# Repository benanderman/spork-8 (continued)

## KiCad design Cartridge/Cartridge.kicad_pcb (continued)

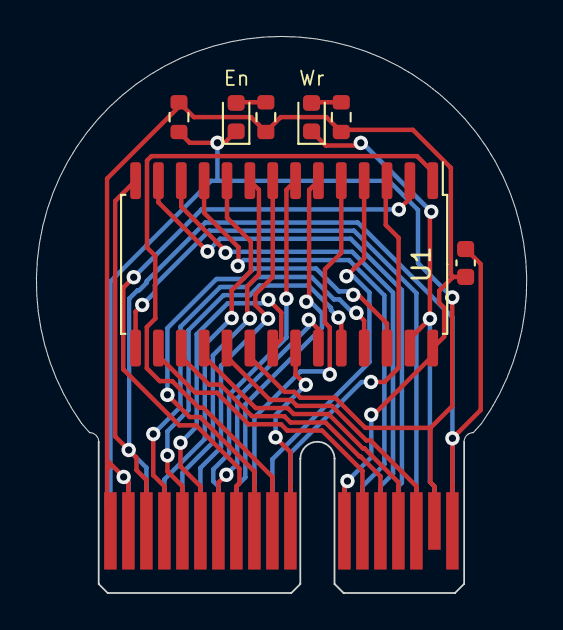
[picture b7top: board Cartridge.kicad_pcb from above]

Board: 2 copper layers, 27.2 x 30.9 mm, 8 parts (0 on the bottom side), 30 nets.

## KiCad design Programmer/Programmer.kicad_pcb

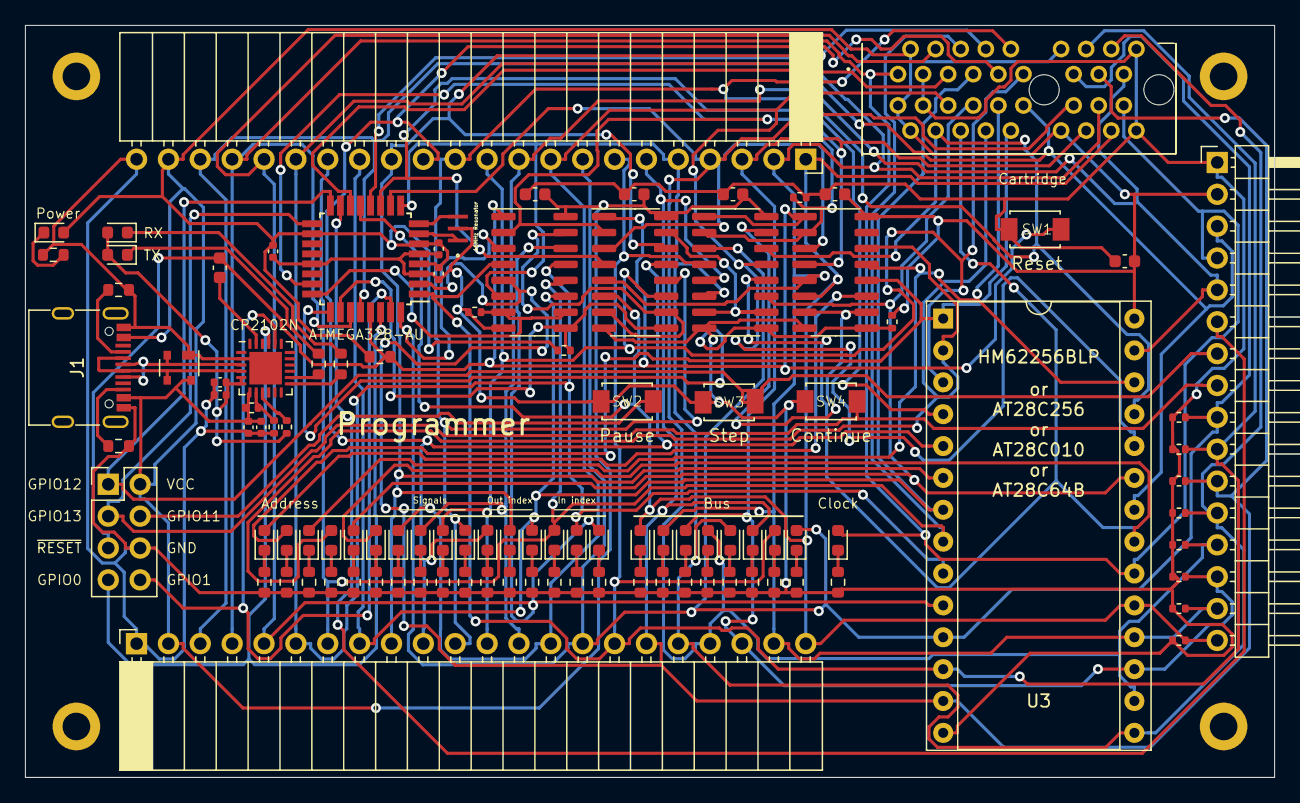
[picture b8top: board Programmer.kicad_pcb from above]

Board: 2 copper layers, 99.6 x 59.9 mm, 110 parts (0 on the bottom side), 82 nets.

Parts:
16MHz1: Resonator; OSC_CSTCE16M0V53-R0
C1, C2, C3, C4, C6: 4.7uF; C_0402_1005Metric
C5, C7: 0.1uF; C_0402_1005Metric
C8, C9, C10, C11, C12, C13: 0.1uF; C_0603_1608Metric
D1, D4: GREEN; LED_0603_1608Metric
D2: SP0503BAHT; SOT-143
D3: RED; LED_0603_1608Metric
D5, D6, D7, D8, D9, D10, D11, D12, D13, D14, D15, D16, D17, D18, D19, D20, D21, D22, D23, D24, D25, D26, D27, D28, D29: LED; LED_0603_1608Metric
HOLE1, HOLE2, HOLE3, HOLE4: MountingHole_2.2mm_M2_DIN965_Pad
J1: USB_C_Receptacle_USB2.0; USB_C_Receptacle_G-Switch_GT-USB-7010ASV
J2, J3: Conn_01x22; PinSocket_1x22_P2.54mm_Horizontal
J4: Conn_01x16; PinHeader_1x16_P2.54mm_Horizontal
J5: 3183-10200P1T; 318310200P1T
J6: Conn_02x04_Odd_Even; PinHeader_2x04_P2.54mm_Vertical
R1, R9: 47k; R_0603_1608Metric
R2, R8, R10, R11, R12, R13, R14, R15, R16, R17, R18, R19, R20, R21, R22, R23, R24, R25, R26, R27, R28, R29, R30, R31, R32, R33, R34: 10k; R_0603_1608Metric
R3, R4: 5.1k; R_0603_1608Metric
R5: 22.1k; R_0402_1005Metric
R6: 47.5k; R_0402_1005Metric
R7: 1k; R_0402_1005Metric
R35, R36, R37, R38, R39, R40, R41, R42, R43, R44, R45, R46: 10k; R_0402_1005Metric
SW1: RESET; SW_TS-1088-AR02016
SW2: PAUSE; SW_TS-1088-AR02016
SW3: STEP; SW_TS-1088-AR02016
SW4: CONTINUE; SW_TS-1088-AR02016
U1: ATMEGA328-AU; TQFP-32_7x7mm_P0.8mm
U2: CP2102N-Axx-xQFN24; QFN-24-1EP_4x4mm_P0.5mm_EP2.6x2.6mm
U3: HM62256BLP; DIP-28_W15.24mm_Socket
U4, U5, U6, U7: 74HC161; SOIC-16_3.9x9.9mm_P1.27mm

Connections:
A0: D5.2 (A), J2.5, J3.18, J5.A4, U3.10 (A0), U4.14 (Q0)
A1: D6.2 (A), J2.6, J3.17, J5.A5, U3.9 (A1), U4.13 (Q1)
A2: D7.2 (A), J2.7, J3.16, J5.A6, U3.8 (A2), U4.12 (Q2)
A3: D8.2 (A), J2.8, J3.15, J5.A7, U3.7 (A3), U4.11 (Q3)
A4: D9.2 (A), J2.9, J3.14, J5.A8, U3.6 (A4), U5.14 (Q0)
A5: D10.2 (A), J2.10, J3.13, J5.A9, U3.5 (A5), U5.13 (Q1)
A6: D11.2 (A), J2.11, J3.12, J5.A10, U3.4 (A6), U5.12 (Q2)
A7: D12.2 (A), J2.12, J3.11, J5.A11, U3.3 (A7), U5.11 (Q3)
A8: D13.2 (A), J2.13, J3.10, J5.B4, U3.25 (A8), U6.14 (Q0)
A9: D14.2 (A), J2.14, J3.9, J5.B5, U3.24 (A9), U6.13 (Q1)
A10: D15.2 (A), J5.B6, U3.21 (A10), U6.12 (Q2)
A11: D16.2 (A), J5.B7, U3.23 (A11), U6.11 (Q3)
A12: D17.2 (A), J5.B8, U3.2 (A12), U7.14 (Q0)
A13: D18.2 (A), J5.B9, U3.26 (A13), U7.13 (Q1)
A14: D19.2 (A), J5.B10, U3.1 (A14), U7.12 (Q2)
A15: D20.2 (A), U7.11 (Q3)
ADDR_CLOCK: R45.2, U1.23 (PC0), U4.2 (CP), U5.2 (CP), U6.2 (CP), U7.2 (CP)
ADDR_COUNT: R46.2, U1.24 (PC1), U4.7 (CEP), U4.10 (CET)
BUS0: D21.2 (A), J2.15, J3.8, J4.9, J5.A13, R35.2, U1.32 (PD2), U3.11 (Q0), U4.3 (D0), U6.3 (D0)
BUS1: D22.2 (A), J2.16, J3.7, J4.10, J5.A14, R36.2, U1.1 (PD3), U3.12 (Q1), U4.4 (D1), U6.4 (D1)
BUS2: D23.2 (A), J2.17, J3.6, J4.11, J5.A15, R37.2, U1.2 (PD4), U3.13 (Q2), U4.5 (D2), U6.5 (D2)
BUS3: D24.2 (A), J2.18, J3.5, J4.12, J5.A16, R38.2, U1.9 (PD5), U3.15 (Q3), U4.6 (D3), U6.6 (D3)
BUS4: D25.2 (A), J2.19, J3.4, J4.13, J5.B13, R39.2, U1.10 (PD6), U3.16 (Q4), U5.3 (D0), U7.3 (D0)
BUS5: D26.2 (A), J2.20, J3.3, J4.14, J5.B14, R40.2, U1.11 (PD7), U3.17 (Q5), U5.4 (D1), U7.4 (D1)
BUS6: D27.2 (A), J2.21, J3.2, J4.15, J5.B15, R41.2, U1.12 (PB0), U3.18 (Q6), U5.5 (D2), U7.5 (D2)
BUS7: D28.2 (A), J2.22, J3.1, J4.16, J5.B16, R42.2, U1.13 (PB1), U3.19 (Q7), U5.6 (D3), U7.6 (D3)
GND: 16MHz1.2, C1.1, C2.1, C3.1, C4.1, C5.1, C6.1, C7.1, C9.2, C10.2, C11.2, C12.2, C13.2, D2.1 (A), J1.A12 (GND), J1.B12 (GND), J2.1, J3.22, J4.1, J5.A3, J5.A18, J5.B3, J5.B18, J6.6, R1.1, R3.1, R4.1, R6.2, R10.2, R11.2, R12.2, R13.2, R14.2, R15.2, R16.2, R17.2, R18.2, R19.2, R20.2, R21.2, R22.2, R23.2, R24.2, R25.2, R26.2, R27.2, R28.2, R29.2, R30.2, R31.2, R32.2, R33.2, R34.2, R35.1, R36.1, R37.1, R38.1, R39.1, R40.1, R41.1, R42.1, R45.1, R46.1, SW1.1, SW2.1, SW3.1, SW4.1, U1.3 (GND), U1.5 (GND), U1.21 (GND), U2.2 (GND), U2.25 (GND), U3.14 (GND), U4.8 (GND), U5.8 (GND), U6.8 (GND), U7.8 (GND)
GPIO10: J4.5, J5.A17, U1.14 (PB2), U3.27 (~WE)
GPIO11: J4.6, J6.4, SW2.2, U1.15 (PB3)
GPIO12: J4.7, J6.1, SW3.2, U1.16 (PB4)
GPIO13: J4.8, J6.3, SW4.2, U1.17 (PB5)
GPIO18: D29.2 (A), J2.4, J3.19, J4.4, J5.A1, J5.B17, U1.27 (PC4), U3.20 (~CS)
GPIO19: J2.3, J3.20, J4.3, J5.B11, U1.28 (PC5), U3.22 (~OE)
unnamed: D1.1 (K), R1.2
unnamed: C6.2, C7.2, D3.2 (A), D4.2 (A), R7.1, U2.5 (VIO), U2.6 (VDD)
unnamed: D3.1 (K), R8.1
unnamed: D4.1 (K), R9.1
unnamed: D5.1 (K), R10.1
unnamed: D6.1 (K), R11.1
unnamed: D7.1 (K), R12.1
unnamed: D8.1 (K), R13.1
unnamed: D9.1 (K), R14.1
unnamed: D10.1 (K), R15.1
unnamed: D11.1 (K), R16.1
unnamed: D12.1 (K), R17.1
unnamed: D13.1 (K), R18.1
unnamed: D14.1 (K), R19.1
unnamed: D15.1 (K), R20.1
unnamed: D16.1 (K), R21.1
unnamed: D17.1 (K), R22.1
unnamed: D18.1 (K), R23.1
unnamed: D19.1 (K), R24.1
unnamed: D20.1 (K), R25.1
unnamed: D21.1 (K), R26.1
unnamed: D22.1 (K), R27.1
unnamed: D23.1 (K), R28.1
unnamed: D24.1 (K), R29.1
unnamed: D25.1 (K), R30.1
unnamed: D26.1 (K), R31.1
unnamed: D27.1 (K), R32.1
unnamed: D28.1 (K), R33.1
unnamed: D29.1 (K), R34.1
unnamed: J1.A5 (CC1), R4.2
unnamed: J1.B5 (CC2), R3.2
unnamed: D2.2 (K), J1.A6 (D+), J1.B6 (D+), U2.3 (D+)
unnamed: D2.3 (K), J1.A7 (D-), J1.B7 (D-), U2.4 (D-)
unnamed: R5.2, R6.1, U2.8 (VBUS)
unnamed: C8.1, U2.23 (~DTR)
unnamed: R7.2, U2.9 (~RST)
unnamed: R9.2, U2.13 (~RXT/GPIO.1)
unnamed: R8.2, U2.14 (~TXT/GPIO.0)
unnamed: U4.15 (TC), U5.7 (CEP), U5.10 (CET)
unnamed: U5.15 (TC), U6.7 (CEP), U6.10 (CET)
unnamed: U6.15 (TC), U7.7 (CEP), U7.10 (CET)
RXD: J6.8, U1.31 (PD1), U2.20 (RXD)
TXD: J6.7, U1.30 (PD0), U2.21 (TXD)
VCC: C1.2, C2.2, C3.2, C4.2, C5.2, C9.1, C10.1, C11.1, C12.1, C13.1, D1.2 (A), D2.4 (K), J1.A9 (VBUS), J1.B9 (VBUS), J2.2, J3.21, J4.2, J5.A2, J5.A12, J5.B1, J5.B2, J5.B12, J6.2, R2.2, R5.1, R43.2, R44.2, U1.4 (VCC), U1.6 (VCC), U1.18 (AVCC), U2.7 (VREGIN), U3.28 (VCC), U4.16 (VCC), U5.16 (VCC), U6.16 (VCC), U7.16 (VCC)
XTAL1: 16MHz1.1, U1.7 (PB6)
XTAL2: 16MHz1.3, U1.8 (PB7)
~ADDR_PE_0: R43.1, U1.26 (PC3), U4.9 (~PE), U5.9 (~PE)
~ADDR_PE_1: R44.1, U1.25 (PC2), U6.9 (~PE), U7.9 (~PE)
~RESET: C8.2, J6.5, R2.1, SW1.2, U1.29 (PC6), U4.1 (~MR), U5.1 (~MR), U6.1 (~MR), U7.1 (~MR)

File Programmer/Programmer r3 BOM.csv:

Designator,Comment,Footprint,LCSC Part Number
16MHz1,Resonator,OSC_CSTCE16M0V53-R0,C32180
"C1, C2, C3, C4, C6",4.7uF,402,C23733
"C5, C7",0.1uF,402,C307331
"C8, C9, C10, C11, C12, C13",0.1uF,603,C14663
"D1, D4",GREEN,603,C965804
D2,SP0503BAHT,SOT-143,C3040626
D3,RED,603,C2286
"D5, D6, D7, D8, D9, D10, D11, D12, D13, D14, D15, D16, D17, D18, D19, D20, D21, D22, D23, D24, D25, D26, D27, D28, D29",LED,603,C2290
J1,USB_C_Receptacle_USB2.0,USB_C_Receptacle_G-Switch_GT-USB-7010ASV,C2988369
"J2, J3",Conn_01x22,PinSocket_1x22_P2.54mm_Horizontal,
J4,Conn_01x16,PinHeader_1x16_P2.54mm_Horizontal,
J5,3183-10200P1T,318310200P1T,
J6,Conn_02x04_Odd_Even,PinHeader_2x04_P2.54mm_Vertical,
"R1, R9",47k,603,C25819
R2,10k,603,C25804
"R3, R4",5.1k,603,C23186
R5,22.1k,402,C25768
R6,47.5k,402,C25792
R7,1k,402,C11702
"R8, R10, R11, R12, R13, R14, R15, R16, R17, R18, R19, R20, R21, R22, R23, R24, R25, R26, R27, R28, R29, R30, R31, R32, R33, R34",10k,603,C25804
"R35, R36, R37, R38, R39, R40, R41, R42, R43, R44, R45, R46",10k,402,C25744
SW1,RESET,SW_TS-1088-AR02016,C720477
SW2,PAUSE,SW_TS-1088-AR02016,C720477
SW3,STEP,SW_TS-1088-AR02016,C720477
SW4,CONTINUE,SW_TS-1088-AR02016,C720477
U1,ATMEGA328-AU,TQFP-32_7x7mm_P0.8mm,C14877
U2,CP2102N-Axx-xQFN24,QFN-24-1EP_4x4mm_P0.5mm_EP2.6x2.6mm,C969151
U3,HM62256BLP,DIP-28_W15.24mm_Socket,
"U4, U5, U6, U7",74HC161,SOIC-16_3.9x9.9mm_P1.27mm,C5310798

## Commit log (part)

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2021-02-09 Update README.md
    Add initial description of project and modules.
2021-02-09 Add design images
2021-02-09 Add layout and signal function images to readme
2021-02-09 Fix case of image URLs in readme
2021-02-09 Add text about empty module slots to readme
2021-03-09 Fixed floating inputs; improved power; added parts list; replaced JK latches
2021-03-09 Update annotation of new chips on clock module
2021-03-09 Add counter images to readme
2021-03-17 Initial code for instruction set
2021-04-14 Revise control and RAM modules
    - Change control signals on low going clock
    - Pull down control signals with 1k resistors
    - AND the write signal with clock on RAM / ROM module
2021-04-18 Add revision log
2021-04-24 Untested code to write to EEPROMs using Spork8 modules and Arduino
2021-04-25 Fix reversed headers on ALU, and counting issues on counter (CET / CEP connections)
2021-04-25 Working Arduino / Spork8 memory test code
2021-04-25 Update memory read/write code for 28C64B
2021-04-26 Code to write microinstructions to EEPROMs
2021-04-26 Add test program
2021-05-05 Add many more, and conditional instructions; update test program to use them
2021-05-05 Add customasm rule gen script; new program generated with customasm
2021-05-06 Add to revision log
2021-05-15 Overhaul instruction set to use all modules; new program that uses it; all untested on hardware
2021-05-16 Some refactors and fixes to instruction set and main code
2021-05-17 Fixes to microcode and program; optimize RAM use and speed for EEPROM writing
2021-05-17 Fix program, and make it display a rectangle
2021-05-17 Fix Not instruction
2021-05-30 Add ShiftL, Mult, conditional ALU calculations, and dynamic mem access
2021-06-28 Add WIP snake game
2021-10-06 Update README.md
    Add a status of the project section.
2025-06-30 Control module sch: remove auto-MI reset; remove control line pull-downs; instruction register, 273 -> 2x173
2025-06-30 Update all boards to r3, and update revision log and gitignore
2025-07-23 Minor update to readme
2025-07-23 Add 7 new board designs
2025-12-08 Update code for 74HC-based CPU and programmer board
2026-01-08 Fix SetPageReg and SetAddrReg microcode
2026-01-19 Update emulation state to use functions to access memory / progmem
2026-01-19 Add no-flags versions of Add/Sub/AND Immediate
2026-01-19 Make gen rules script support instructions with constants
2026-01-19 Add support for programmer used as progmem / clock
2026-01-19 Random file PCB updates
2026-01-19 Add assembly programs
2026-01-19 Add emulator code in Zig
2026-01-19 Update revision log
2026-01-31 Add increasing speed to snake game
2026-01-31 Remove other programs from root.zig
2026-01-31 Use clock LED to signify write success on programmer
2026-01-31 Optimize RAM use when writing instruction set
2026-01-31 Fix formatting
2026-01-31 Update programs and function signature in Arduino code
2026-01-31 Update moving dot program to not use Call instruction
2026-01-31 Update images and readme
2026-04-19 Invert carry flag behavior in emulator to match hardware
2026-04-20 Update snake game to work on hardware / fix carry flag
2026-04-20 Update moving dot program to fix small bug and not us ZP
2026-04-20 Add script to update programs.cpp from asm file
2026-04-21 Update programs.cpp with current asm content
2026-05-02 Update snake game, to make it start 1/5 the speed
2026-05-02 Make bus board 4L with ground planes and extra GND connectors
2026-05-02 Fix issue with snake teleporting every 255 iterations
2026-05-02 Make food in snake not spawn on top of snake
2026-05-17 Add memory edit program
2026-05-19 Add address to right column of memory edit program
2026-05-19 Move gen_customasm_rules script into Code/
2026-05-26 Update emulator code for Zig 16
2026-05-26 Update instruction set, and asm generator
2026-06-07 Fix some bugs with the instruction set update; use Call / Return in Snake
